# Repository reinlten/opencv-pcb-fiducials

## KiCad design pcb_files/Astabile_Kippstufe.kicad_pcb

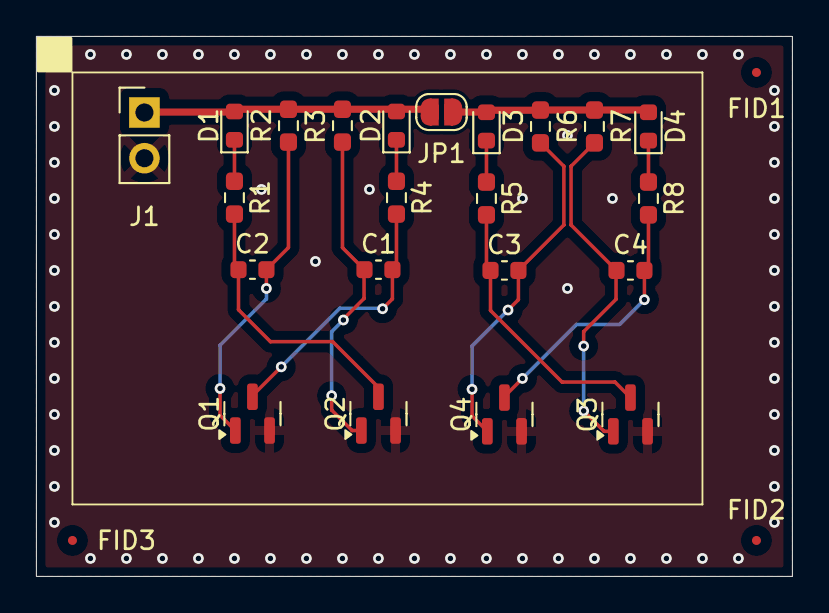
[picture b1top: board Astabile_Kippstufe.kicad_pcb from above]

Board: 2 copper layers, 42.0 x 30.0 mm, 25 parts (0 on the bottom side), 15 nets.

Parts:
C1, C2, C3, C4: 10µ; C_0603_1608Metric
D1, D2, D3, D4: LED; LED_0603_1608Metric
FID1, FID2, FID3: Fiducial; Fiducial_0.5mm_Mask1.5mm
J1: Conn_01x02_Pin; PinHeader_1x02_P2.54mm_Vertical
JP1: Jumper_2_Open; SolderJumper-2_P1.3mm_Open_RoundedPad1.0x1.5mm
Q1, Q2, Q3, Q4: BC847; SOT-23
R1, R4, R5, R8: 470; R_0603_1608Metric_Pad0.98x0.95mm_HandSolder
R2, R3: 47k; R_0603_1608Metric_Pad0.98x0.95mm_HandSolder
R6, R7: 100k; R_0603_1608Metric_Pad0.98x0.95mm_HandSolder

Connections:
+9V: D1.2 (A), D2.2 (A), J1.1, JP1.1 (A), R2.1, R3.1
GND: J1.2, Q1.2 (E), Q2.2 (E), Q3.2 (E), Q4.2 (E)
unnamed: D1.1 (K), R1.1
unnamed: D2.1 (K), R4.1
unnamed: D3.2 (A), D4.2 (A), JP1.2 (B), R6.1, R7.1
unnamed: D3.1 (K), R5.1
unnamed: D4.1 (K), R8.1
unnamed: C2.2, Q1.1 (B), R2.2
unnamed: C1.2, Q1.3 (C), R4.2
unnamed: C1.1, Q2.1 (B), R3.2
unnamed: C2.1, Q2.3 (C), R1.2
unnamed: C4.1, Q3.1 (B), R7.2
unnamed: C3.1, Q3.3 (C), R5.2
unnamed: C3.2, Q4.1 (B), R6.2
unnamed: C4.2, Q4.3 (C), R8.2
